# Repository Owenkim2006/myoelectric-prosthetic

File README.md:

# Myoelectric Prosthetic Hand

**BME 261 Final Project** · University of Waterloo · August 2026  

---

## Overview

This project develops a functional myoelectric prosthetic hand for transradial amputees performing demanding tasks. The system converts microvolt-level surface EMG signals into mechanical grip control through three integrated subsystems: a 7-stage analog front-end, non-blocking C++ firmware, and a dog clutch locking mechanism.

Benchmarked against the Cybathlon "Carry Bottles" task — gripping weighted bottles, placing them into a crate, and transporting the load.

---

## System Architecture

```
Surface EMG Electrodes
        │
        ▼
┌─────────────────────────────────────┐
│     7-Stage Analog Front-End        │
│                                     │
│  1. AD623 INA (gain ~101)           │
│  2. Sallen-Key HPF (48 Hz)          │
│  3. Sallen-Key LPF (400 Hz)         │
│  4. Isolation Buffer                │
│  5. Non-Inverting Amp (gain 11)     │
│  6. Peak Envelope Detector          │
│  7. Schmitt Trigger Comparator      │
│                                     │
│  Total gain: ~1,111×                │
└──────────────────┬──────────────────┘
                   │  Digital trigger (0–5V)
                   ▼
        Arduino Microcontroller
        (Non-blocking state machine)
                   │
                   ▼
          Position Servo Motor
                   │
                   ▼
            Dog Clutch
     (locks finger transmission shafts)
                   │
                   ▼
      Passive Spring-Loaded Fingers
```

---

## Electrical Subsystem

The analog front-end processes raw surface EMG signals (10μV–5mV) through a cascaded 7-stage single-supply architecture.

### Signal Chain

| Stage | Component | Function | Key Parameters |
|---|---|---|---|
| 1 | AD623 INA | Differential amplification, CM rejection | Gain ~101, R_G = 1kΩ |
| 2 | Sallen-Key HPF | Remove motion artifacts, electrode drift | f_c ≈ 48 Hz, C = 33nF, R = 1MΩ / 10kΩ |
| 3 | Sallen-Key LPF | Remove high-frequency noise | f_c ≈ 400 Hz, R = 20kΩ, C = 12nF / 33nF |
| 4 | Buffer (follower) | Isolation — prevent impedance loading | Unity gain |
| 5 | Non-inverting amp | Secondary voltage gain | Gain = 11, R_in = 10kΩ, R_f = 100kΩ |
| 6 | Peak detector | Rectify AC bursts to DC envelope | Active diode-capacitor |
| 7 | Schmitt trigger | Clean binary output to Arduino | Hysteretic comparator |

**Total system gain: ~1,111×**

### Virtual Ground

A buffered voltage divider (2× 10kΩ) creates a stable Vcc/2 reference, enabling single-supply operation. The reference automatically scales with battery voltage — no recalibration needed when switching between lab supply and battery.

### Power

- Lab: regulated DC supply (5V)
- Portable: dual 4×AA packs in parallel (~6V, doubled current capacity)

### Frequency Response

Measured passband: 48–400 Hz. Overdamped filter design produces gradual roll-off at corner frequencies.

---

## Firmware

Written in C++ on Arduino. Non-blocking time-domain state machine — no `delay()` calls.

### State Machine

```
         ┌─────────────────┐
         │      IDLE       │
         └────────┬────────┘
                  │ Edge detected on input pin
                  ▼
         ┌─────────────────┐
         │  BURST ACTIVE   │◄──────────────┐
         │  (timing burst) │               │ Still toggling
         └────────┬────────┘               │
                  │ Duration ≥ 500ms        │
                  ▼                        │
         ┌─────────────────┐               │
         │    ACTUATE      │               │
         │  Toggle servo   │               │
         │  Set lock flag  │               │
         └────────┬────────┘               │
                  │ Signal static > 400ms   │
                  ▼                        │
         ┌─────────────────┐               │
         │  RESET LOCKOUT  │───────────────┘
         │  Clear flags    │
         └─────────────────┘
```

### Key Parameters

| Parameter | Value | Purpose |
|---|---|---|
| `activityWindow` | 500 ms | Minimum contraction duration — rejects twitches and noise spikes |
| `quietTimeout` | 400 ms | Rest period required before next trigger |
| Servo open | 135° | Dog clutch disengaged — fingers free |
| Servo closed | 150° | Dog clutch engaged — fingers locked |

### Why these values?

The 500ms window was chosen to eliminate false triggers from static shocks, brief muscle twitches, and electrical noise while remaining responsive enough for intentional grips. The 400ms quiet timeout prevents rapid re-triggering during a single sustained contraction. Servo angles are software-clamped to prevent mechanical binding and the 2.5A stall current observed near 170°.

---

## Mechanical Subsystem

- **Fingers:** Two interconnected phalange sections (base + top) coordinated by sprockets, chains, and gears
- **Actuation:** Passive spring loading — fingers open when pressed against object geometry
- **Locking:** Dog clutch controlled by position servo — mechanically retains grip with zero steady-state motor current
- **Structure:** Laser-cut plywood with box-joint connections, aluminum axles

### Finger Movement

When the hand contacts an object, friction and reaction forces passively open the fingers to conform to the object geometry. The internal spring tension closes the fingers around the object. On muscle activation, the servo engages the dog clutch, locking the transmission shafts and holding the grip position.

---

## Repository Structure

```
myoelectric-prosthetic/
  firmware/
    prosthetic_control.ino     # Arduino C++ state machine
    flowchart.png              # Firmware flowchart
  electrical/
    bodeplots.png             # Bode plots
    schematic.png              # Full system schematic
    falstad_diagram.txt                # Falstad simulation export
  pcb/
    gerbers/                   # Fabrication files
    prosthetic_pcb.kicad_pcb   # KiCad board file
    prosthetic.kicad_sch       # KiCad schematic
    bom.csv                    # Bill of materials
  mechanical/
    presentation.pdf
  docs/
    BME261_Final_Report.pdf    # Full project report
    bill_of_materials.pdf      # List of parts
```

---

## Running the Falstad Simulation

1. Open [Falstad Circuit Simulator](https://www.falstad.com/circuit/)
2. Click **File → Import from Text**
3. Paste the contents of `electrical/falstad/circuit.txt`
4. Press **Run** to simulate the signal conditioning pipeline

---

## Results

| Metric | Result |
|---|---|
| Signal passband | 48–400 Hz |
| Total analog gain | ~1,111× |
| EMG input range | 10μV–5mV |
| Output range | 0–5V (Arduino compatible) |
| Trigger delay | 500ms (intentional) |
| Servo travel | 135°–150° |
| Cybathlon task | Successfully demonstrated |
| PCB | 2-layer through-hole, 0.4mm signal / 0.8mm power traces |
| Ground | Solid B.Cu copper pour, thermal relief on all pads |
| DRC | 0 errors, 0 unconnected items |

---

## Limitations & Future Work

- **Materials:** PETG components and superglue connections loosened during testing. Future: engineering-grade heat-resistant materials, pinned dog clutch connection
- **Firmware:** 500ms window reduces responsiveness. Future: continuous ADC sampling with digital moving-average filter, shorter activation window
- **Electrical:** Hand-soldered perfboard susceptible to EMI and stray capacitance. Future: multi-layer SMD PCB, LDO regulator for analog supply, buck-boost for servo
- **Power:** Unregulated battery causes reference drift as charge depletes. Future: dedicated LDO for analog front-end
- **Mechanical:** Smooth plastic palm reduces friction on objects. Future: compliant grip surface material

---

## Built With

- **Electrical:** AD623, TL072/TL082 op-amps, discrete passives
- **Simulation:** [Falstad Circuit Simulator](https://www.falstad.com/circuit/)
- **PCB:** KiCad
- **Mechanical:** Autodesk Fusion 360, laser-cut plywood, PETG 3D printing
- **Firmware:** Arduino (C++)
- **Course:** BME 261 — Biomedical Design, University of Waterloo

---

## Authors

- Owen Kim — Electrical subsystem, firmware, PCB design
- Adithi Nagarajan — Mechanical subsystem
- Hilda Zhang — Mechanical subsystem

---

## License

MIT — free to use, adapt, and build on with attribution.

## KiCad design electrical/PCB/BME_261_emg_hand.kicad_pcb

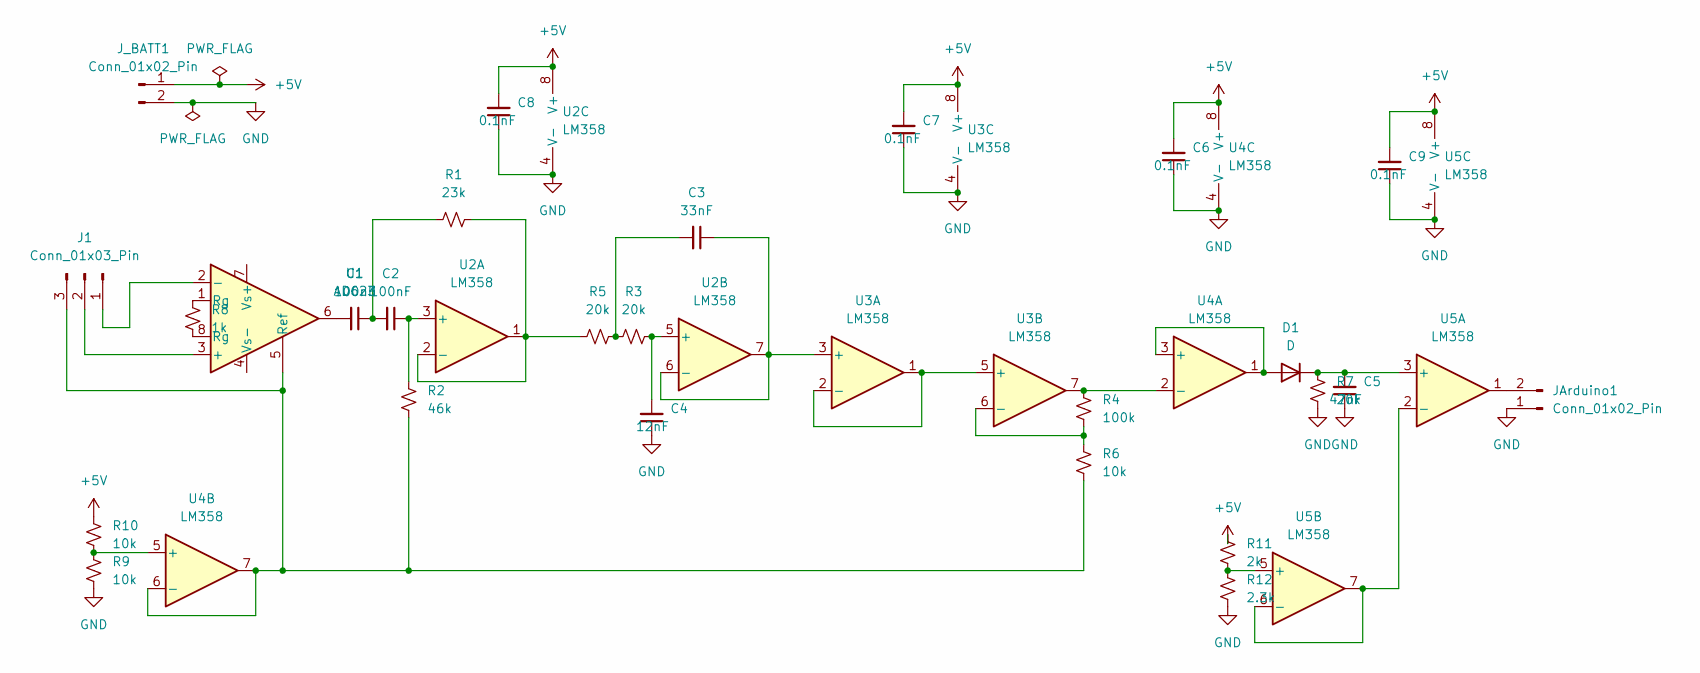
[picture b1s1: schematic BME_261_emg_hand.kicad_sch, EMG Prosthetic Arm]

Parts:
C1, C2: 100nF; C_Disc_D5.0mm_W2.5mm_P5.00mm
C3: 33nF; C_Disc_D5.0mm_W2.5mm_P5.00mm
C4: 12nF; C_Disc_D5.0mm_W2.5mm_P5.00mm
C5: 47nF; C_Disc_D5.0mm_W2.5mm_P5.00mm
C6, C7, C8, C9: 0.1nF; C_Disc_D5.0mm_W2.5mm_P5.00mm
D1: D; D_DO-35_SOD27_P7.62mm_Horizontal
J1: Conn_01x03_Pin; PinHeader_1x03_P2.54mm_Vertical
JArduino1: Conn_01x02_Pin; PinHeader_1x02_P2.54mm_Vertical
J_BATT1: Conn_01x02_Pin; PinHeader_1x02_P2.54mm_Vertical
R1: 23k; R_Axial_DIN0207_L6.3mm_D2.5mm_P7.62mm_Horizontal
R2: 46k; R_Axial_DIN0207_L6.3mm_D2.5mm_P7.62mm_Horizontal
R3, R5, R7: 20k; R_Axial_DIN0207_L6.3mm_D2.5mm_P7.62mm_Horizontal
R4: 100k; R_Axial_DIN0207_L6.3mm_D2.5mm_P7.62mm_Horizontal
R6, R9, R10: 10k; R_Axial_DIN0207_L6.3mm_D2.5mm_P7.62mm_Horizontal
R8: 1k; R_Axial_DIN0207_L6.3mm_D2.5mm_P7.62mm_Horizontal
R11: 2k; R_Axial_DIN0207_L6.3mm_D2.5mm_P7.62mm_Horizontal
R12: 2.3k; R_Axial_DIN0207_L6.3mm_D2.5mm_P7.62mm_Horizontal
U1: AD623; DIP-8_W7.62mm_SMDSocket_SmallPads
U2, U3, U4, U5: LM358; DIP-8_W7.62mm

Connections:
+5V: C6.2, C7.2, C8.2, C9.2, J_BATT1.1, R10.2, R11.2, U2.8 (V+), U3.8 (V+), U4.8 (V+), U5.8 (V+)
GND: C4.1, C5.1, C6.1, C7.1, C8.1, C9.1, JArduino1.1, J_BATT1.2, R7.1, R9.1, R12.1, U2.4 (V-), U3.4 (V-), U4.4 (V-), U5.4 (V-)
unnamed: C1.1, C2.2, R1.2
unnamed: C1.2, U1.6
unnamed: C3.2, R3.1, R5.1
unnamed: D1.2 (A), U4.1, U4.3 (+)
unnamed: C5.2, D1.1 (K), R7.2, U5.3 (+)
unnamed: J1.1, U1.2 (-)
unnamed: J1.2, U1.3 (+)
unnamed: J1.3, R2.1, R6.1, U1.5 (Ref), U4.6 (-), U4.7
unnamed: JArduino1.2, U5.1
unnamed: R8.1, U1.8 (Rg)
unnamed: R8.2, U1.1 (Rg)
unnamed: C2.1, R2.2, U2.3 (+)
unnamed: R1.1, R5.2, U2.1, U2.2 (-)
unnamed: C4.2, R3.2, U2.5 (+)
unnamed: C3.1, U2.6 (-), U2.7, U3.3 (+)
unnamed: U3.1, U3.2 (-), U3.5 (+)
unnamed: R4.1, R6.2, U3.6 (-)
unnamed: R4.2, U3.7, U4.2 (-)
unnamed: R9.2, R10.1, U4.5 (+)
unnamed: U5.2 (-), U5.6 (-), U5.7
unnamed: R11.1, R12.2, U5.5 (+)

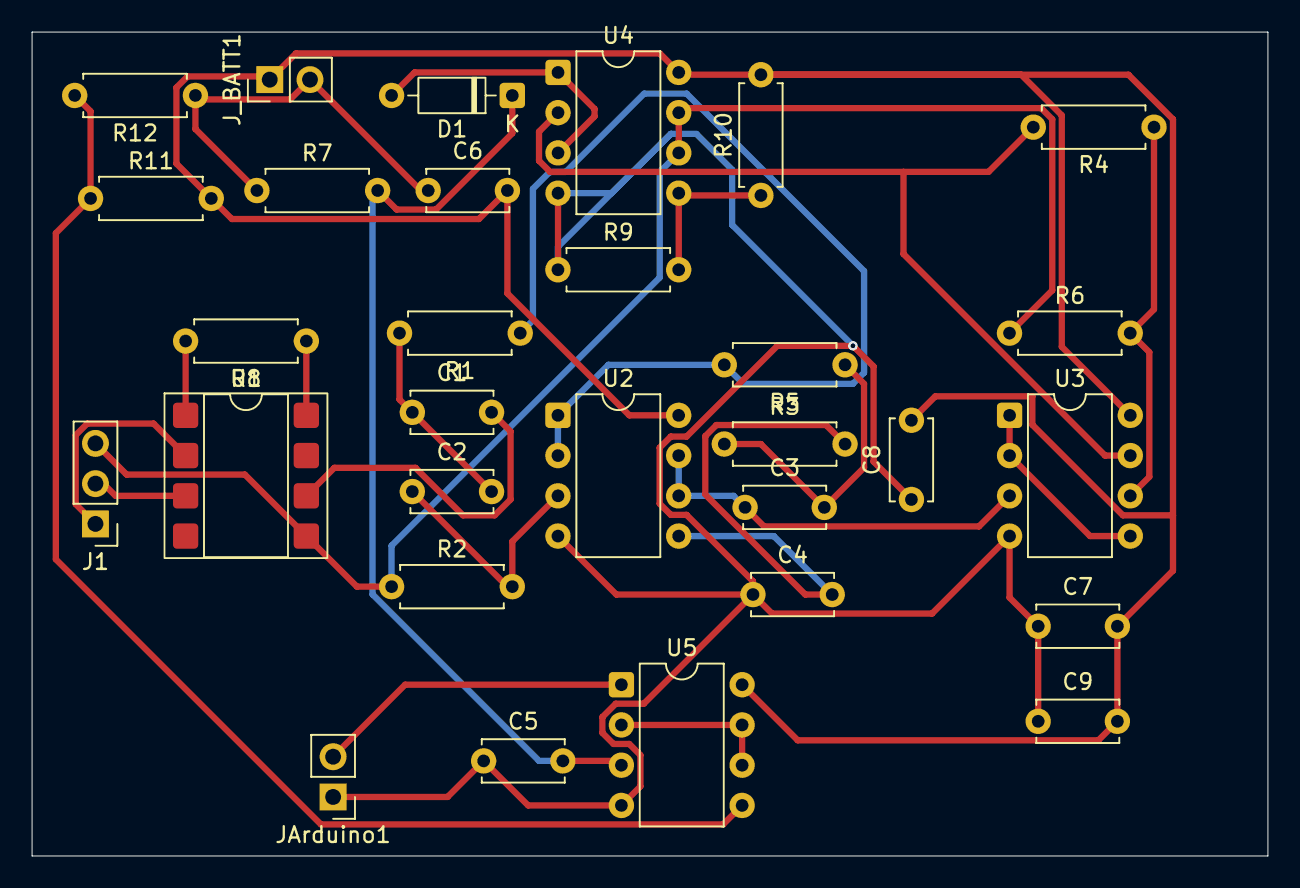
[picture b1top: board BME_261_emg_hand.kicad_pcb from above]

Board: 2 copper layers, 78.0 x 52.0 mm, 30 parts (0 on the bottom side), 23 nets.
